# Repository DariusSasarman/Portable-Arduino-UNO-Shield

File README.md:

# Portable-Arduino-UNO-Shield

## What is it?

A shield that you can use to upgrade older Arduino UNO boards such that your projects don't need extra batteries nor cables. Just the one your phone uses!

## How does it look?

## Physical details:
- **Input:** USB-C (5V, up to 2A for charging)
- **Battery:** 14500 Li-ion Rechargeable (3.7V, 500mAh)
- **Output:** 5V through boost converter ( -0.6V diode voltage drop when running on usb-c !!! )
- **Board Size:** Aprox. 91.5 × 53.4 mm

## Main components
- **Charging IC:** Handles the Li-ion charging (MCP73831-2-OT)
- **Boost Converter:** Steps up 3.7V from the battery to 5V for the Arduino (TPS61200DRC)
- **MOSFET:** Disconects the battery from output when current is fed from USB (PMOS)
- **Reverse Blocking Diode:** Makes sure current doesn't flow backward
- **ESD Diode:** Protects against static discharge on the USB data lines (USBLC6-2SC6)
- **USB to UART converter:** Translates the data lines to actual information (CH340E)

## Installation & usage
1. Pop the 14500 battery into the holder(  Watch the polarity!)
2. Stack the shield onto your Arduino UNO
3. Plug in USB-C to charge (the LED being on means the battery charging)
4. When done charging, unplug and turn on the switch!

## Schematic

## How would this prove useful?

Ever had a project that needed the arduino to be mounted somewhere such that a USB connection couldn't have been possible? I did.

## How did I make it?

I build it by integrating both a standard Li-ion charging circuit (MCP73831 reference design) with a boost converter topology and a USB-serial interface. Added my own custom changes to these, such as the LED and battery switch. It has been a wonderful experiment.

**Key Learnings:** decoupling capacitors, pull-down resistors, step-up boost converters usage, usb-to-uart translation as a requirement.

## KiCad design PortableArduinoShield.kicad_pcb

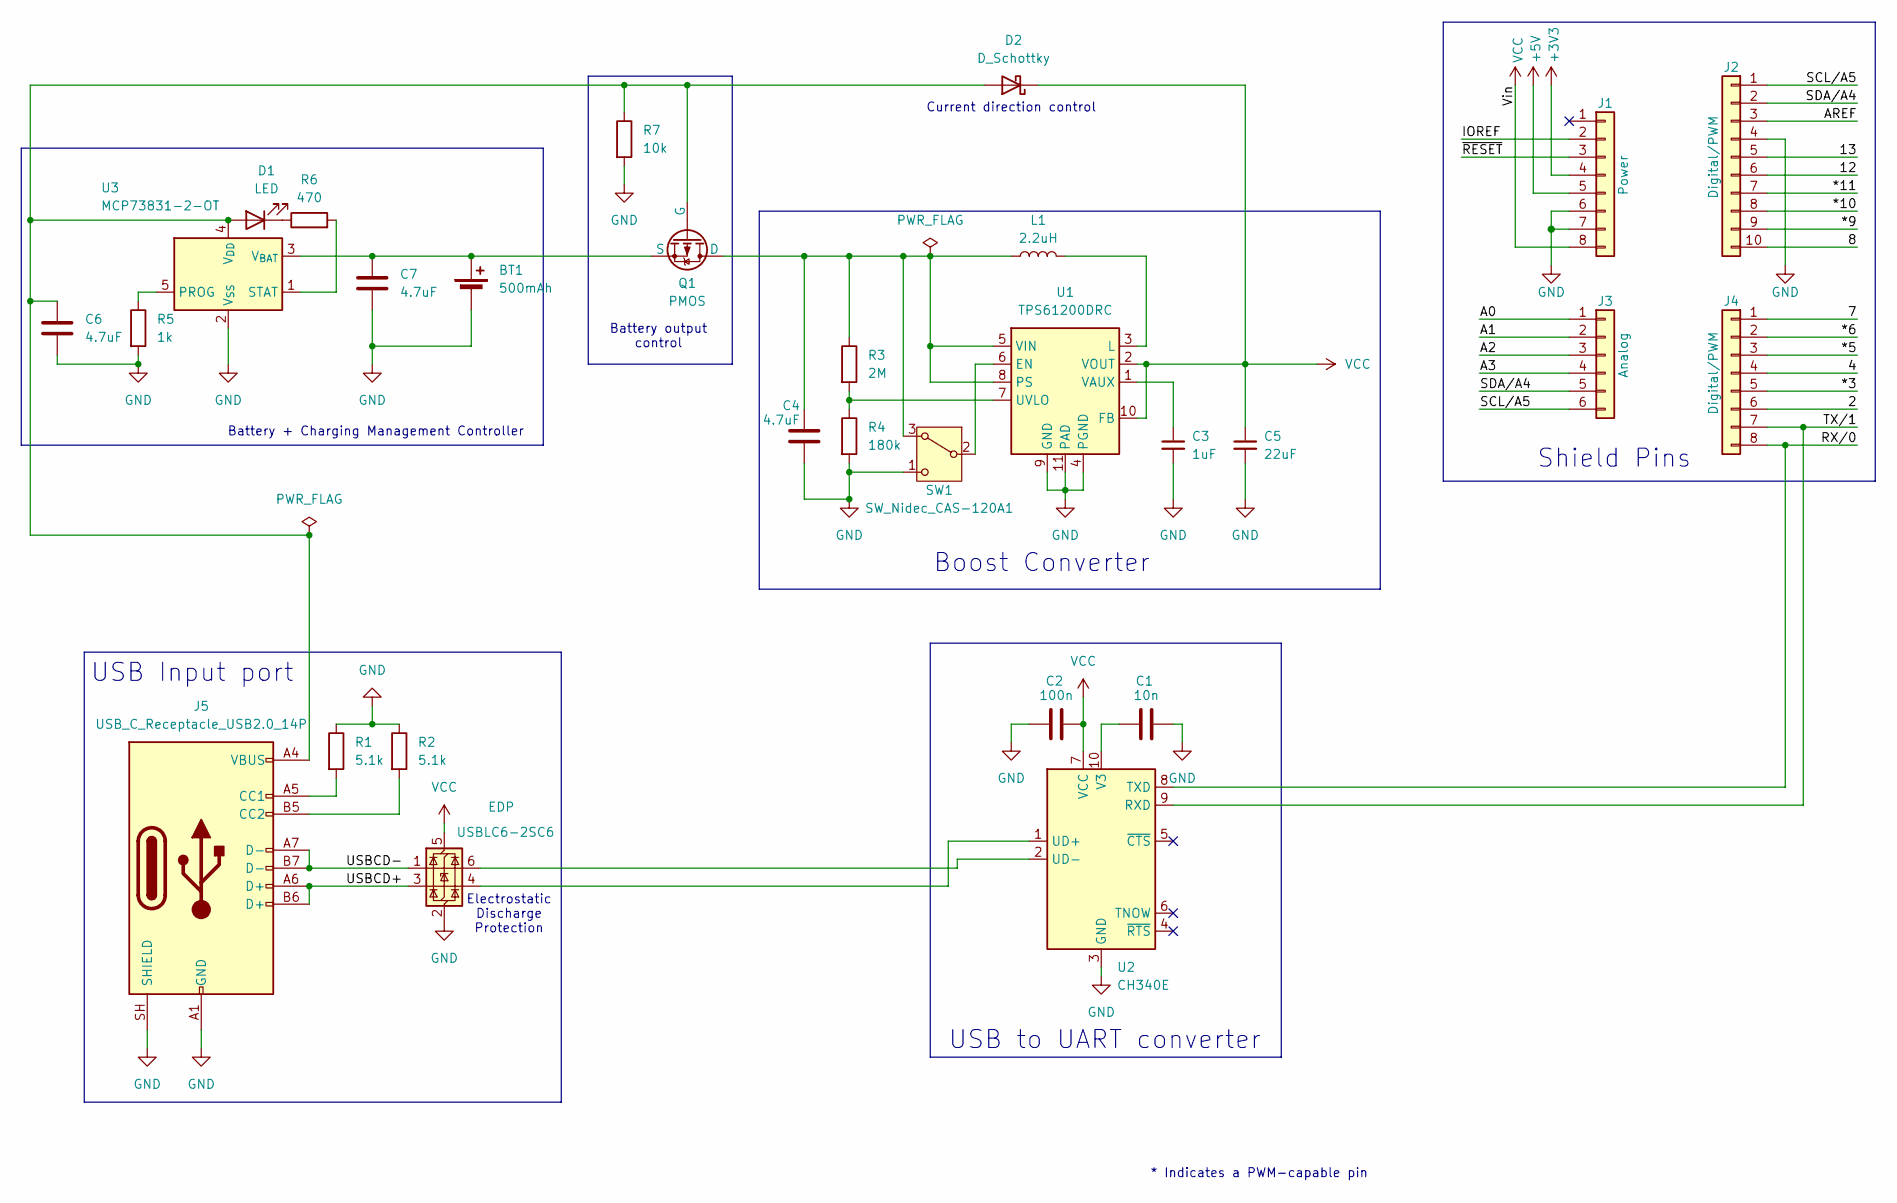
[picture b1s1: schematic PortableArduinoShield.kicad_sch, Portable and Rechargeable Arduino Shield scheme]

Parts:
BT1: 500mAh; BatteryHolder_Keystone_1042_1x18650
C1: 10n; C_0603_1608Metric
C2: 100n; C_0603_1608Metric
C3: 1uF; C_0603_1608Metric
C4, C6, C7: 4.7uF; C_0603_1608Metric
C5: 22uF; C_0603_1608Metric
D1: LED; LED_0603_1608Metric
D2: D_Schottky; D_SOD-123
EDP: USBLC6-2SC6; SOT-23-6
J1: Power; PinSocket_1x08_P2.54mm_Vertical
J2: Digital/PWM; PinSocket_1x10_P2.54mm_Vertical
J3: Analog; PinSocket_1x06_P2.54mm_Vertical
J4: Digital/PWM; PinSocket_1x08_P2.54mm_Vertical
J5: USB_C_Receptacle_USB2.0_14P; USB_C_Receptacle_Amphenol_12401610E4-2A
L1: 2.2uH; L_Bourns-SRN4018
Q1: PMOS; SOT-23
R1, R2: 5.1k; R_0603_1608Metric
R3: 2M; R_0603_1608Metric
R4: 180k; R_0603_1608Metric
R5: 1k; R_0603_1608Metric
R6: 470; R_0603_1608Metric
R7: 10k; R_0603_1608Metric
SW1: SW_Nidec_CAS-120A1; SW_Slide_SPDT_Straight_CK_OS102011MS2Q
U1: TPS61200DRC; Texas_S-PVSON-N10_ThermalVias
U2: CH340E; MSOP-10_3x3mm_P0.5mm
U3: MCP73831-2-OT; SOT-23-5

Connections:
+3V3: J1.4
+5V: J1.5
/2: J4.6
/4: J4.4
/7: J4.1
/8: J2.10
/12: J2.6
/13: J2.5
/*3: J4.5
/*5: J4.3
/*6: J4.2
/*9: J2.9
/*10: J2.8
/*11: J2.7
/A0: J3.1
/A1: J3.2
/A2: J3.3
/A3: J3.4
/AREF: J2.3
/IOREF: J1.2
/RX/0: J4.8, U2.8 (TXD)
/SCL/A5: J2.1, J3.6
/SDA/A4: J2.2, J3.5
/TX/1: J4.7, U2.9 (RXD)
/USBCD+: EDP.3 (I/O2), J5.A6 (D+), J5.B6 (D+); also elsewhere on the board
/USBCD-: EDP.1 (I/O1), J5.A7 (D-), J5.B7 (D-); also elsewhere on the board
/~RESET: J1.3
GND: BT1.2 (-), C1.1, C2.2, C3.2, C4.2, C5.2, C6.2, C7.2, EDP.2 (GND), J1.6, J1.7, J2.4, J5.A1 (GND), J5.A12 (GND), J5.B1 (GND), J5.B12 (GND), J5.SH (SHIELD), R1.1, R2.1, R4.2, R5.2, R7.2, SW1.1 (C), U1.4 (PGND), U1.9 (GND), U1.11 (PAD), U2.3 (GND), U3.2 (V_{SS}); also elsewhere on the board
unnamed: BT1.1 (+), C7.1, Q1.3 (S), U3.3 (V_{BAT})
unnamed: C6.1, D1.2 (A), D2.2 (A), J5.A4 (VBUS), J5.A9 (VBUS), J5.B4 (VBUS), J5.B9 (VBUS), Q1.2 (G), R7.1, U3.4 (V_{DD})
unnamed: D1.1 (K), R6.1
unnamed: J5.A5 (CC1), R1.2
unnamed: J5.B5 (CC2), R2.2
unnamed: C4.1, L1.1, Q1.1 (D), R3.1, SW1.3 (A), U1.5 (VIN), U1.8 (PS)
unnamed: SW1.2 (B), U1.6 (EN)
unnamed: L1.2, U1.3 (L)
unnamed: R3.2, R4.1, U1.7 (UVLO)
unnamed: C3.1, U1.1 (VAUX)
unnamed 38: EDP.4 (I/O2), U2.1 (UD+); also elsewhere on the board
unnamed 39: EDP.6 (I/O1), U2.2 (UD-); also elsewhere on the board
unnamed: C1.2, U2.10 (V3)
unnamed: R5.1, U3.5 (PROG)
unnamed: R6.2, U3.1 (STAT)
VCC: C2.1, C5.1, D2.1 (K), EDP.5 (VBUS), J1.8, U1.2 (VOUT), U1.10 (FB), U2.7 (VCC); also elsewhere on the board

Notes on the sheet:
USB Input port
Battery output control
USB to UART converter
Shield Pins
Current direction control
Electrostatic Discharge Protection
Battery + Charging Management Controller
* Indicates a PWM-capable pin
Boost Converter

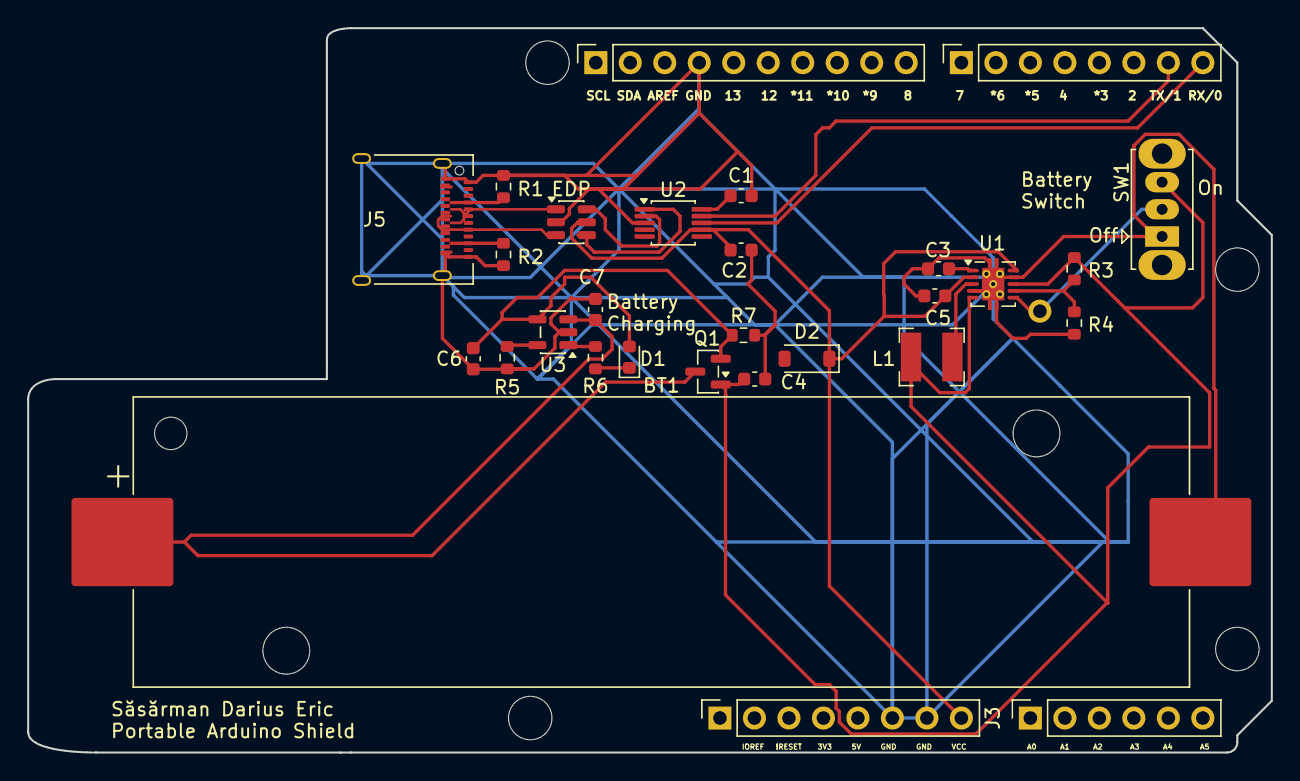
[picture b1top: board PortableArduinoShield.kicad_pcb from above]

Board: 2 copper layers, 91.6 x 53.3 mm, 33 parts (0 on the bottom side), 23 nets.

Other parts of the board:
MH1, MH2, MH3, MH4: MountingHole_3.2mm
VCC1: USBLC6-2SC6; SOT-23-6

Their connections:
/USBCD+: VCC1.3 (I/O2); also elsewhere on the board
/USBCD-: VCC1.1 (I/O1); also elsewhere on the board
GND: VCC1.2 (GND); also elsewhere on the board
unnamed 38: VCC1.4 (I/O2); also elsewhere on the board
unnamed 39: VCC1.6 (I/O1); also elsewhere on the board
VCC: VCC1.5 (VBUS); also elsewhere on the board

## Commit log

2026-06-17 Update README with project details and image
    Added project description and image to README.
2026-06-17 Enhance README with detailed project information
    Added physical details, main components, installation instructions, and personal insights about the project.
2026-06-17 Add KiCad badge to README
2026-06-17 Add KiCad file types to .gitattributes
